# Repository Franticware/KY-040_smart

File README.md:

# KY-040_smart
MCU-driven smart replacement for KY-040 rotary encoder module

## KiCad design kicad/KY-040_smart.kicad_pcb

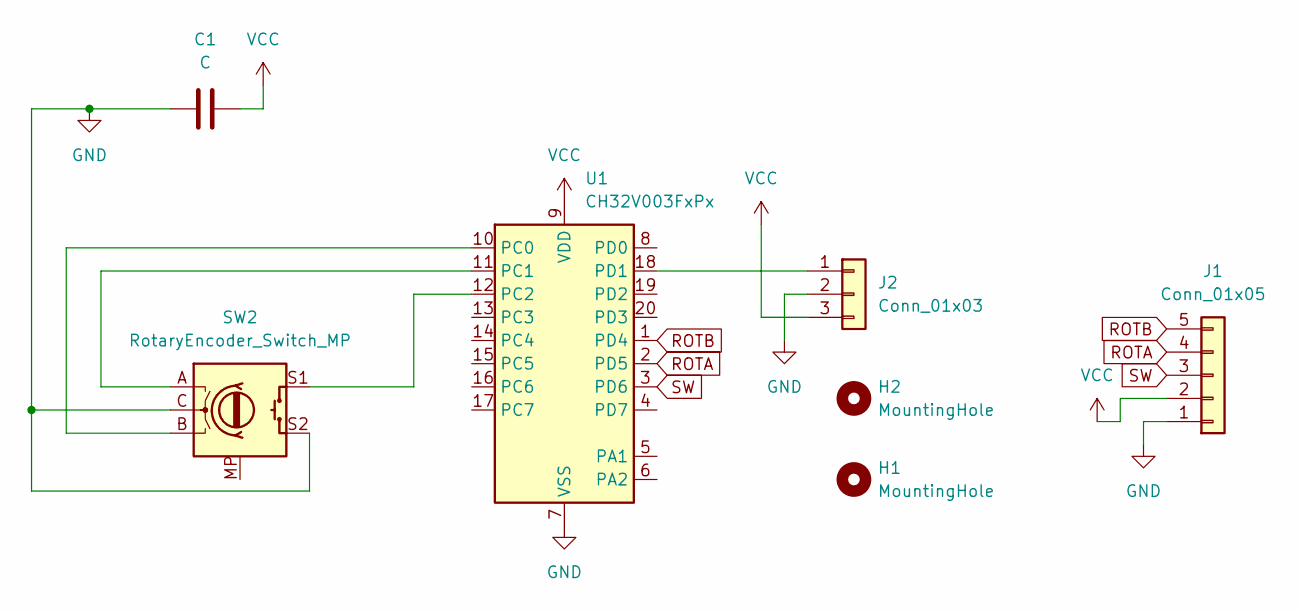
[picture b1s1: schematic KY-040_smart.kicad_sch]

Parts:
C1: C; C_0603_1608Metric_Pad1.08x0.95mm_HandSolder
H1, H2: MountingHole; MountingHole_2.5mm
J1: Conn_01x05; PinHeader_1x05_P2.54mm_Vertical
J2: Conn_01x03; PinHeader_1x03_P2.54mm_Vertical
SW2: RotaryEncoder_Switch_MP; RotaryEncoder_Alps_EC11E-Switch_Vertical_H20mm
U1: CH32V003FxPx; TSSOP-20_4.4x6.5mm_P0.65mm

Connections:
GND: C1.1, J1.1, J2.2, SW2.C, SW2.S2, U1.7 (VSS)
unnamed: J2.1, U1.18 (PD1)
unnamed: SW2.B, U1.10 (PC0)
unnamed: SW2.A, U1.11 (PC1)
unnamed: SW2.S1, U1.12 (PC2)
ROTA: J1.4, U1.2 (PD5)
ROTB: J1.5, U1.1 (PD4)
SW: J1.3, U1.3 (PD6)
VCC: C1.2, J1.2, J2.3, U1.9 (VDD)

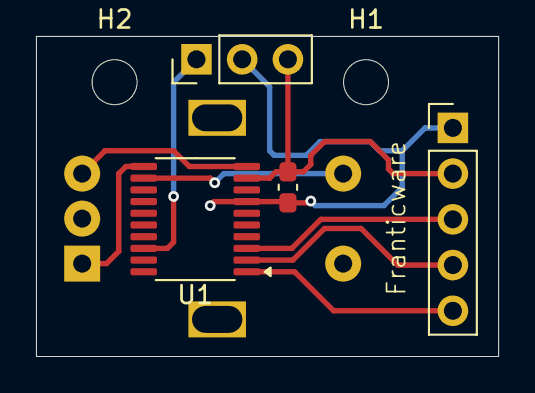
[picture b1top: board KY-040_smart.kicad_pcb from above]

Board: 2 copper layers, 25.7 x 17.8 mm, 7 parts (1 on the bottom side), 9 nets.

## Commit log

2025-02-12 Initial project
2025-02-12 Add smart rotary encoder implementation
2025-02-12 Add KiCad project
2025-05-27 Change outputs from push-pull to open drain.
2025-05-27 Add queue overflow protection.
